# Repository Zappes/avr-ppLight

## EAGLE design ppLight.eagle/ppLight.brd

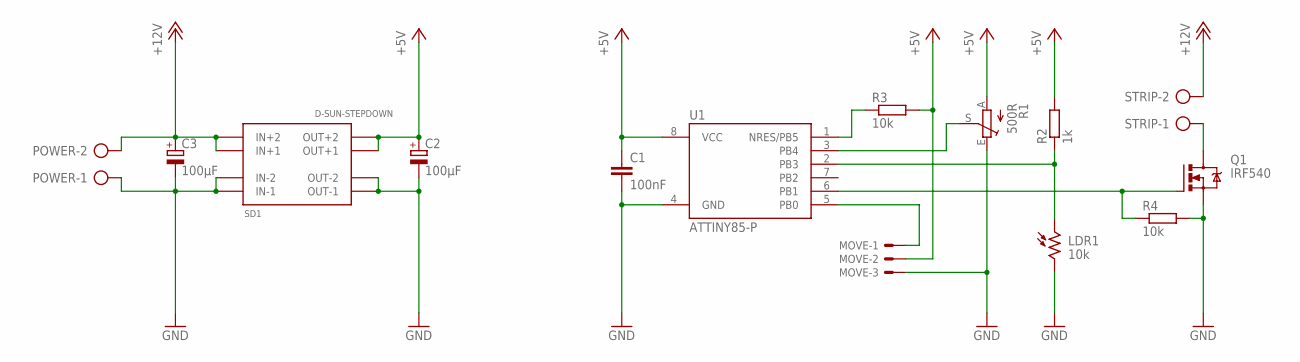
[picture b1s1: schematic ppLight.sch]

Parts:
C1: 100nF; C025-025X050
C2, C3: 100µF; E2,5-5
LDR1: 10k; VT900
MOVE: 22-05-7038-03; 7395-03
POWER: AK500/2
Q1: IRF540; TO220BV
R1: 500R; CT6
R2: 1k; 0204/7
R3, R4: 10k; 0204/7
SD1: D-SUN-STEPDOWN; STEPDOWN-21X16
STRIP: AK500/2
U1: ATTINY85-P; PDIP08_300MIL

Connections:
+5V: C1.1, C2.+, MOVE.2, R1.A, R2.2, R3.2, SD1.OUT+1, SD1.OUT+2, U1.8 (VCC)
+12V: C3.+, POWER.2, SD1.IN+1, SD1.IN+2, STRIP.2
GND: C1.2, C2.-, C3.-, LDR1.2, MOVE.3, POWER.1, Q1.S, R1.E, R4.2, SD1.IN-1, SD1.IN-2, SD1.OUT-1, SD1.OUT-2, U1.4 (GND)
unnamed: R1.S, U1.3 (PB4)
unnamed: Q1.D, STRIP.1
unnamed: R3.1, U1.1 (NRES/PB5)
unnamed: Q1.G, R4.1, U1.6 (PB1)
unnamed: LDR1.1, R2.1, U1.2 (PB3)
unnamed: MOVE.1, U1.5 (PB0)

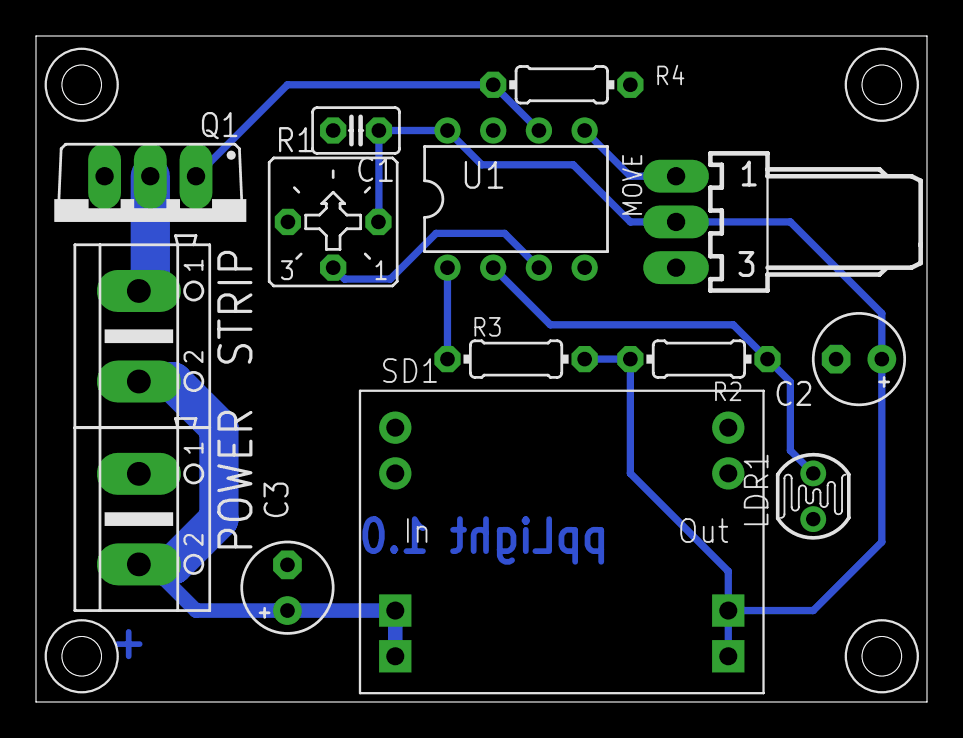
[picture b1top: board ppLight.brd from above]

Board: 2 copper layers, 49.5 x 37.0 mm, 14 parts (0 on the bottom side), 9 nets.

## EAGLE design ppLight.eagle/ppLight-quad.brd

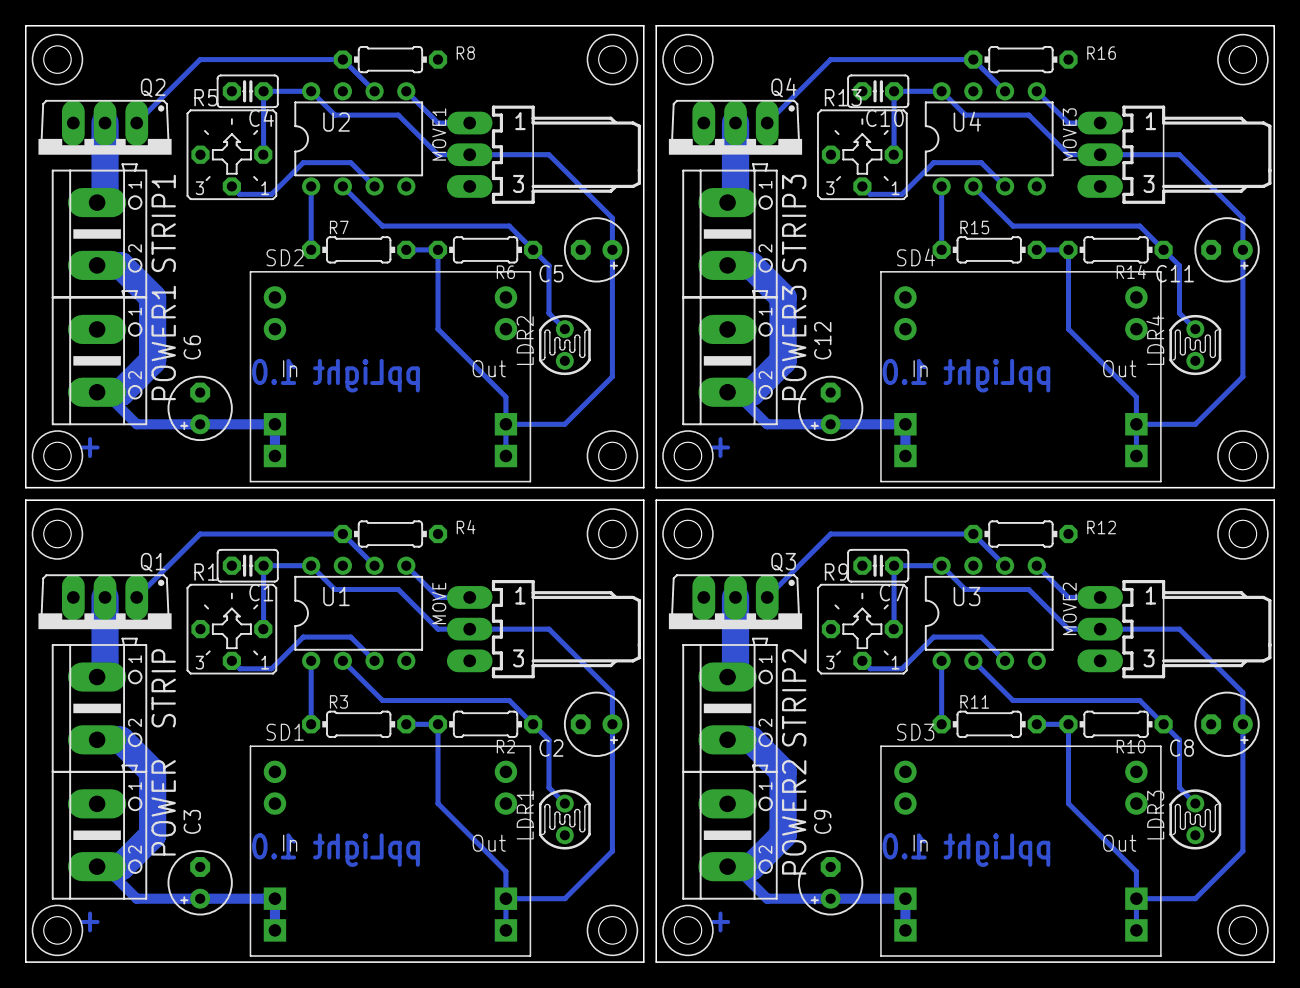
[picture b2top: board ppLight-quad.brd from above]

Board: 2 copper layers, 100.0 x 75.0 mm, 56 parts (0 on the bottom side), 36 nets.

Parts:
C1, C4, C7, C10: 100nF; C025-025X050
C2, C3, C5, C6, C8, C9, C11, C12: 100µF; E2,5-5
LDR1, LDR2, LDR3, LDR4: 10k; VT900
MOVE, MOVE1, MOVE2, MOVE3: 7395-03
POWER, POWER1, POWER2, POWER3: AK500/2
Q1, Q2, Q3, Q4: IRF540; TO220BV
R1, R5, R9, R13: 500R; CT6
R2, R6, R10, R14: 1k; 0204/7
R3, R4, R7, R8, R11, R12, R15, R16: 10k; 0204/7
SD1, SD2, SD3, SD4: D-SUN-STEPDOWN; STEPDOWN-21X16
STRIP, STRIP1, STRIP2, STRIP3: AK500/2
U1, U2, U3, U4: ATTINY85-P; PDIP08_300MIL

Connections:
+5V: C1.1, C2.+, MOVE.2, R1.A, R2.2, R3.2, SD1.OUT+1, SD1.OUT+2, U1.8
+5V1: C4.1, C5.+, MOVE1.2, R5.A, R6.2, R7.2, SD2.OUT+1, SD2.OUT+2, U2.8
+5V2: C7.1, C8.+, MOVE2.2, R9.A, R10.2, R11.2, SD3.OUT+1, SD3.OUT+2, U3.8
+5V3: C10.1, C11.+, MOVE3.2, R13.A, R14.2, R15.2, SD4.OUT+1, SD4.OUT+2, U4.8
+12V: C3.+, POWER.2, SD1.IN+1, SD1.IN+2, STRIP.2
+12V1: C6.+, POWER1.2, SD2.IN+1, SD2.IN+2, STRIP1.2
+12V2: C9.+, POWER2.2, SD3.IN+1, SD3.IN+2, STRIP2.2
+12V3: C12.+, POWER3.2, SD4.IN+1, SD4.IN+2, STRIP3.2
GND: C1.2, C2.-, C3.-, LDR1.2, MOVE.3, POWER.1, Q1.S, R1.E, R4.2, SD1.IN-1, SD1.IN-2, SD1.OUT-1, SD1.OUT-2, U1.4
GND1: C4.2, C5.-, C6.-, LDR2.2, MOVE1.3, POWER1.1, Q2.S, R5.E, R8.2, SD2.IN-1, SD2.IN-2, SD2.OUT-1, SD2.OUT-2, U2.4
GND2: C7.2, C8.-, C9.-, LDR3.2, MOVE2.3, POWER2.1, Q3.S, R9.E, R12.2, SD3.IN-1, SD3.IN-2, SD3.OUT-1, SD3.OUT-2, U3.4
GND3: C10.2, C11.-, C12.-, LDR4.2, MOVE3.3, POWER3.1, Q4.S, R13.E, R16.2, SD4.IN-1, SD4.IN-2, SD4.OUT-1, SD4.OUT-2, U4.4
unnamed: R1.S, U1.3
unnamed: Q1.D, STRIP.1
unnamed: R3.1, U1.1
unnamed: Q1.G, R4.1, U1.6
unnamed: LDR1.1, R2.1, U1.2
unnamed: MOVE.1, U1.5
unnamed: R7.1, U2.1
unnamed: Q2.G, R8.1, U2.6
unnamed: LDR2.1, R6.1, U2.2
unnamed: R5.S, U2.3
unnamed: Q2.D, STRIP1.1
unnamed: MOVE1.1, U2.5
unnamed: R11.1, U3.1
unnamed: Q3.G, R12.1, U3.6
unnamed: LDR3.1, R10.1, U3.2
unnamed: R9.S, U3.3
unnamed: Q3.D, STRIP2.1
unnamed: MOVE2.1, U3.5
unnamed: R15.1, U4.1
unnamed: Q4.G, R16.1, U4.6
unnamed: LDR4.1, R14.1, U4.2
unnamed: R13.S, U4.3
unnamed: Q4.D, STRIP3.1
unnamed: MOVE3.1, U4.5

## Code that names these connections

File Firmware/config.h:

#include <avr/io.h>

#define PORT	PORTB
#define PIN		PINB
#define DDR		DDRB

#define PIN_MOVE	PB0
#define PIN_STRIP	PB1

#define PIN_LIGHT	PB3
#define PIN_TRIM	PB4
#define ADC_LIGHT	3
#define ADC_TRIM	2

// the time the light stays on after the last motion detection.
// expressed in timer ticks which have a freq of 122hz, i.e. use 122 for 1 second.
// should be at least 3 seconds because of the re-arming delay of the PIR
#define TIMER_DELAY 366

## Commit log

2015-03-04 Initial commit of the ppLight source tree
2015-03-05 Moved Firmware to a separate dirctory
2015-03-05 Created Eagle schematics and a board layout.
2015-03-08 Wrapped everything up.
